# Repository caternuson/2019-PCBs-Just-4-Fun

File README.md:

# 2019-PCBs-Just-4-Fun
One PCB a month. Just 4 Fun.

# January

USB powered tamagotchi thing with an ATtiny85 brain.

# February

A backlit commemorative plaque thing.

# March
 <br/>
An IoT pyramid thing.

# April
 <br/>
Optical encoder reader with SPI interface.

# May
 <br/>
Terminal block to breadboard adapter.

# June
 <br/>
JST PH 4 to breadboard adapter.

# July
 <br/>
JST SH 4 to breadboard adapter.

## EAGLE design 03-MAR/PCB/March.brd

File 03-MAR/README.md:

# NOTES

The goal here was to utilize OSHPark's 3x board copy to make a pyramid.

My attempt at making break away mouse bites did not work. Ended up needing to dremel off the side triangles.

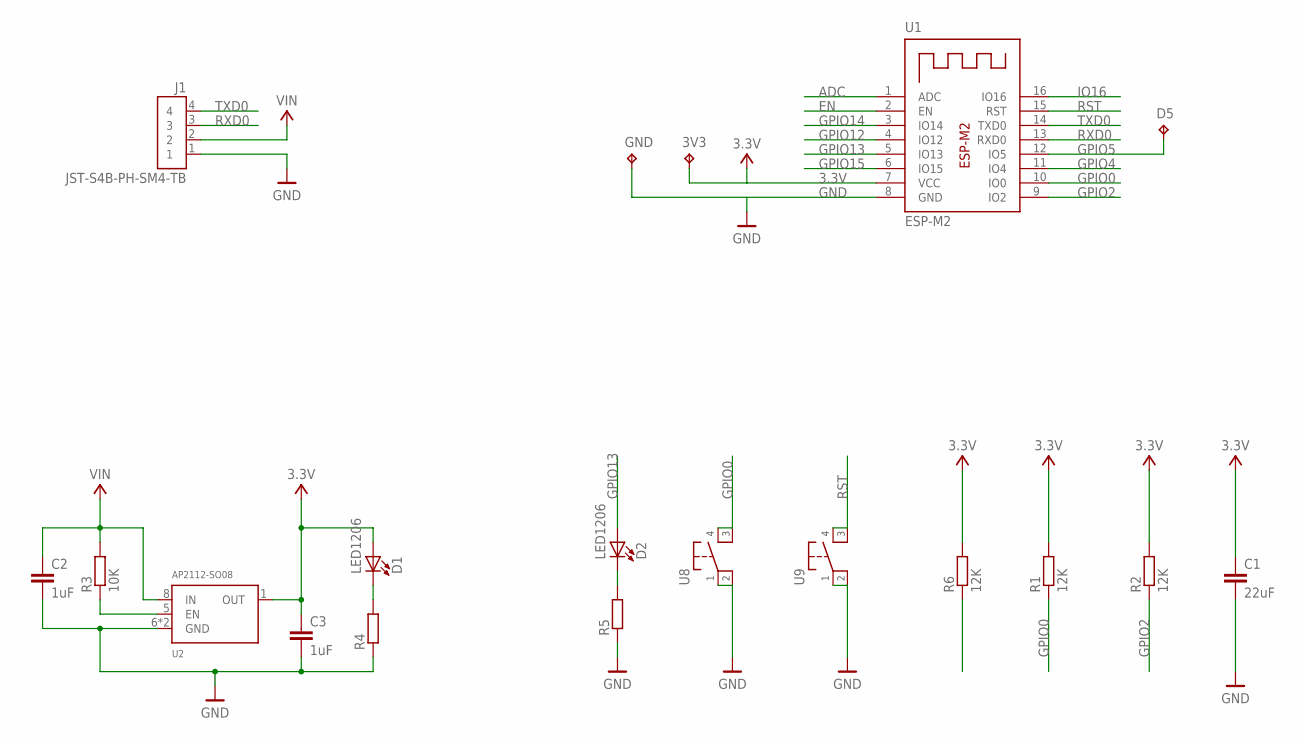
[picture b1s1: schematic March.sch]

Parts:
3V3: TPTP16R; TP16R
C1: 22uF; C1206
C2, C3: 1uF; C1206
D1, D2: LED1206
D5: TPTP16R; TP16R
GND: TPTP16R; TP16R
J1: JST-S4B-PH-SM4-TB
R1, R2, R6: 12K; R1206
R3: 10K; R1206
R4, R5: R-EU_R1206; R1206
U1: ESP-M2
U2: AP2112-SO08; SO08
U8, U9: PTS647

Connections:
3.3V: 3V3.TP, C1.1, C3.1, D1.2 (A), R1.2, R2.2, R6.2, U1.7 (VCC), U2.1 (OUT)
ADC: U1.1 (ADC)
EN: R6.1, U1.2 (EN)
GND: C1.2, C2.2, C3.2, GND.TP, J1.1, R4.1, R5.1, U1.8 (GND), U2.6 (GND), U2.7 (GND), U8.1, U8.2, U9.1, U9.2
GPIO0: R1.1, U1.10 (IO0), U8.3, U8.4
GPIO2: R2.1, U1.9 (IO2)
GPIO4: U1.11 (IO4)
GPIO5: D5.TP, U1.12 (IO5)
GPIO12: U1.4 (IO12)
GPIO13: D2.2 (A), U1.5 (IO13)
GPIO14: U1.3 (IO14)
GPIO15: U1.6 (IO15)
IO16: U1.16 (IO16)
unnamed: D1.1 (C), R4.2
unnamed: R3.1, U2.5 (EN)
unnamed: D2.1 (C), R5.2
RST: U1.15 (RST), U9.3, U9.4
RXD0: J1.3, U1.13 (RXD0)
TXD0: J1.4, U1.14 (TXD0)
VIN: C2.1, J1.2, R3.2, U2.8 (IN)

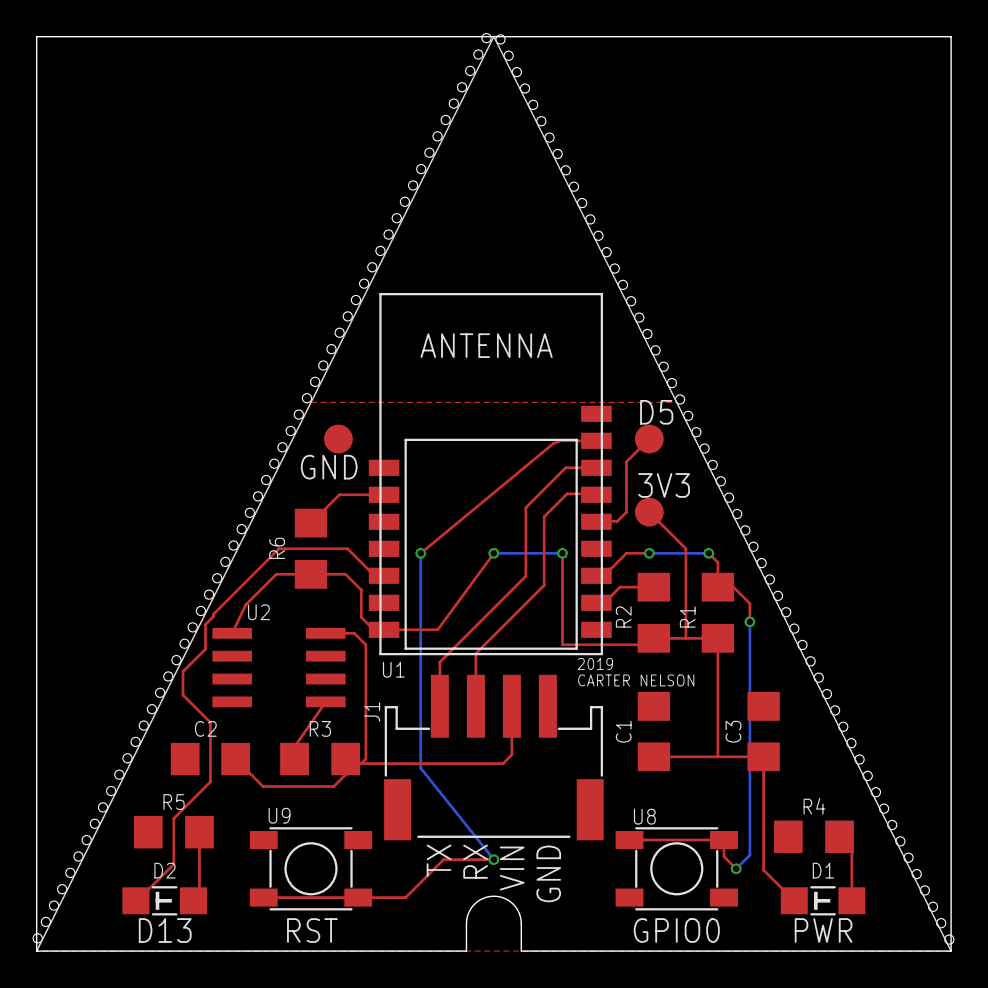
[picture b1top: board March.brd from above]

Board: 2 copper layers, 50.8 x 50.8 mm, 19 parts (0 on the bottom side), 14 nets.

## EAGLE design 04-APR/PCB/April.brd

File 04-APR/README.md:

# NOTES

The goal here was to make a functional breakout for the LS7366R.

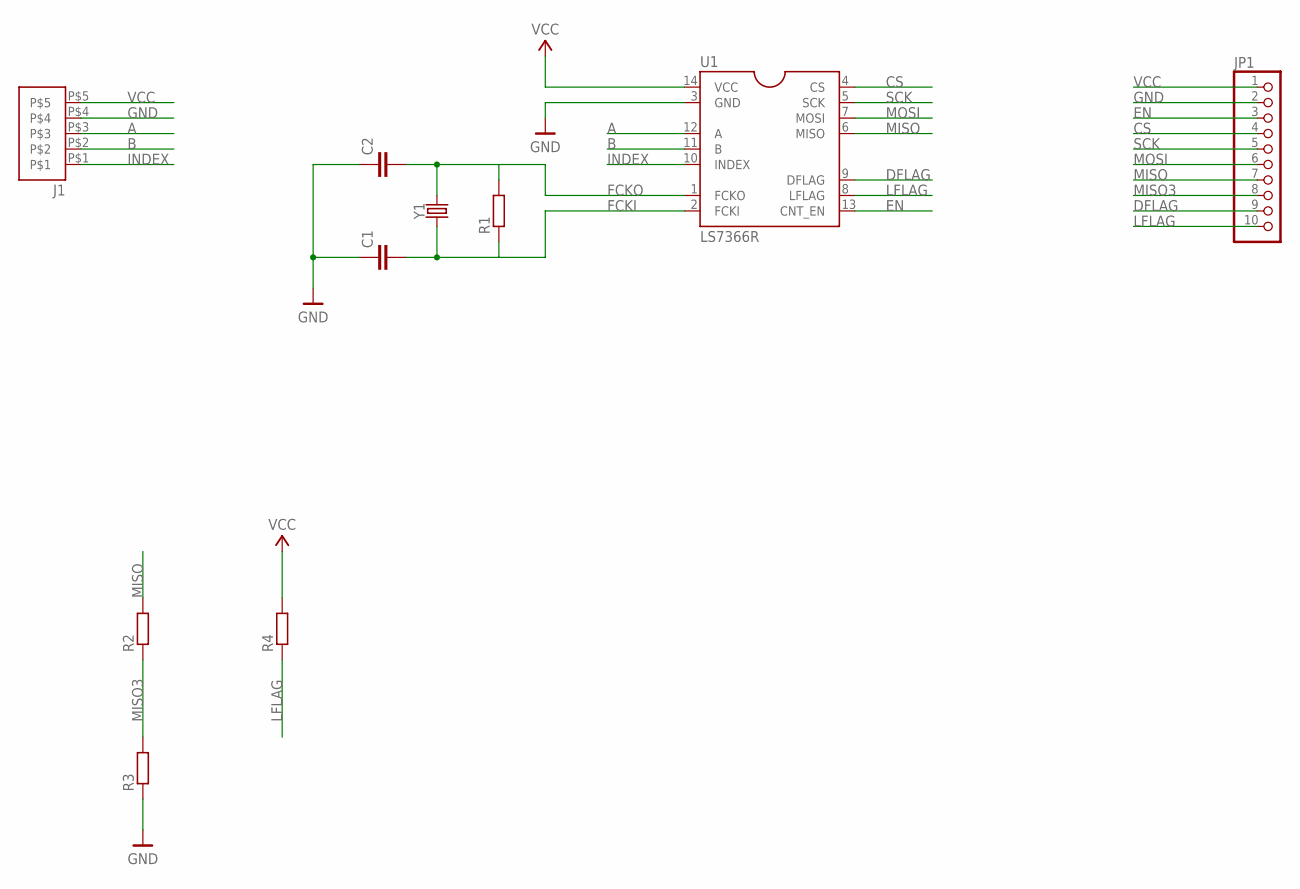
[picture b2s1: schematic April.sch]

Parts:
C1, C2: C-EU050-024X044; C050-024X044
J1: AF-PID2319; TB-01-5
JP1: PINHD-1X10; 1X10
R1, R2, R3, R4: R-EU_0207/10; 0207/10
U1: LS7366R; DIL14
Y1: CRYSTALPTH-HC49US; HC49US

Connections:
A: J1.P$3, U1.12 (A)
B: J1.P$2, U1.11 (B)
CS: JP1.4, U1.4 (CS)
DFLAG: JP1.9, U1.9 (DFLAG)
EN: JP1.3, U1.13 (CNT_EN)
FCKI: C1.2, R1.1, U1.2 (FCKI), Y1.1
FCKO: C2.2, R1.2, U1.1 (FCKO), Y1.2
GND: C1.1, C2.1, J1.P$4, JP1.2, R3.1, U1.3 (GND)
INDEX: J1.P$1, U1.10 (INDEX)
LFLAG: JP1.10, R4.1, U1.8 (LFLAG)
MISO: JP1.7, R2.2, U1.6 (MISO)
MISO3: JP1.8, R2.1, R3.2
MOSI: JP1.6, U1.7 (MOSI)
SCK: JP1.5, U1.5 (SCK)
VCC: J1.P$5, JP1.1, R4.2, U1.14 (VCC)

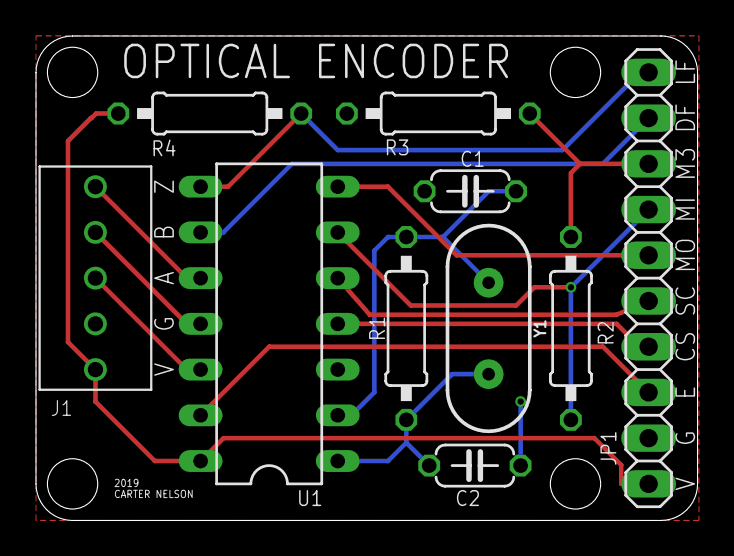
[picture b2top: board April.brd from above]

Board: 2 copper layers, 36.8 x 26.9 mm, 10 parts (0 on the bottom side), 15 nets.

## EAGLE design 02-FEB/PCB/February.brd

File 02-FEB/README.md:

# NOTES

The goal here was to work on the process for bringing in custom art for silk, etc.

### The Process
This process could be generalized to anything that produces a BMP. However, using Inkscape made setting the document properties easier.

* Inkscape
  * Set up document to match board dimensions
  * Make drawing
  * Export PNG
  * Set DPI, ex: 300
* Convert to BMP
  * since Inkscape only exports PNG and Eagle only imports BMP
  * linux convert
    * `convert bitmap.png -background white -alpha remove -alpha off -colors 2 bitmap.bmp`
  * Gimp (old)
    * Convert PNG to BMP
    * Reduce colors
      * Image -> Mode -> Indexed
      * set Maximum number of colors to something small
* Eagle
  * File -> Import -> Bitmap...
  * match DPI to above
  * pick color and destination layer

### Multi-layer specifics
When you import the BMP into Eagle you can specify any destination layer. This lets you
get creative with things like the stop layer to expose copper. The general process that
was done for this board went something like:

* Inkscape
  * Create layers to match the Eagle layers names
    * tPlace
    * tStop
    * etc.
  * Set the colors for these layers to match board fab
    * tPlace = white for silk
    * tStop = yellow-ish for exposed copper
  * Make the layer specific drawings on these layers
  * Output multipe PNGs
    * Turn off all other layers
    * Export to PNG with visible layer name, ex: tPlace.png
  * Convert PNGs as above
  * When importing in Eagle, match the name to the layer

For example, these were the BMPs used for the top silk layer:

and the top stop layer:

which combined to form the white silk and exposed copper:

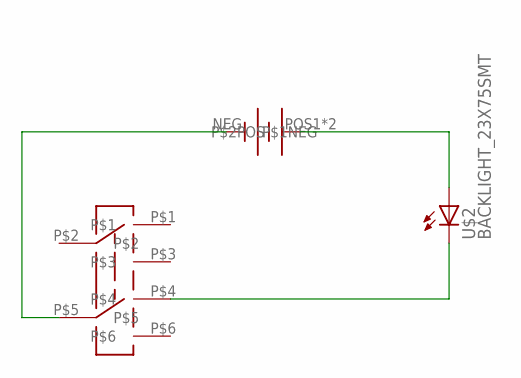
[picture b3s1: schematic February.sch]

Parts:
U$1: JS202011SCQN
U$2: BACKLIGHT_23X75SMT
U$3: BK-912

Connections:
GND: U$1.P$5, U$3.NEG (P$1NEG)
unnamed: U$2.LED+ (A), U$3.POS1 (P$2POS), U$3.POS2 (P$2POS)
VBAT: U$1.P$4, U$2.LED- (C)

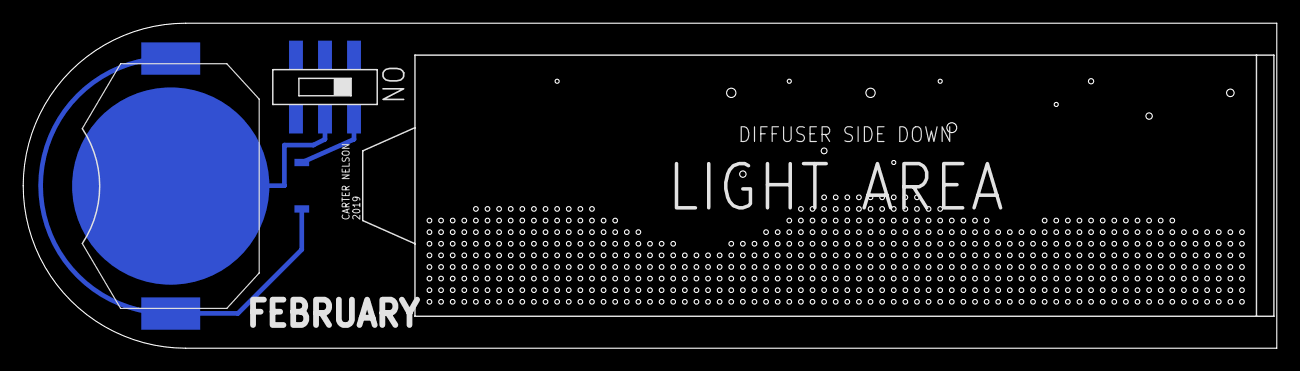
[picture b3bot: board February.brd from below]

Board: 2 copper layers, 108.0 x 28.0 mm, 3 parts (3 on the bottom side), 3 nets.

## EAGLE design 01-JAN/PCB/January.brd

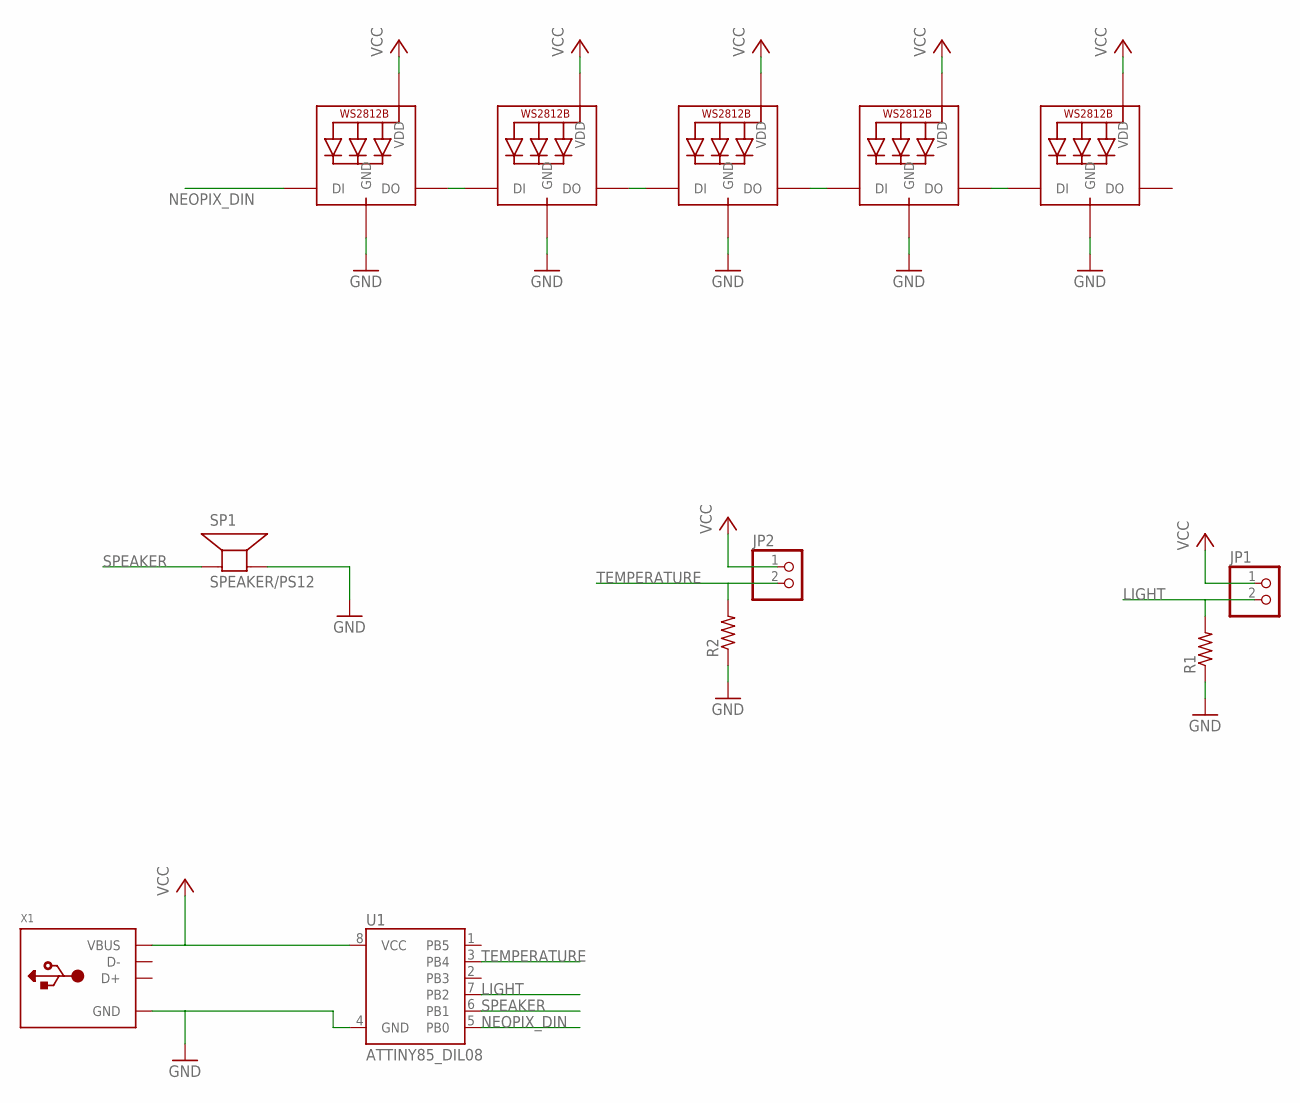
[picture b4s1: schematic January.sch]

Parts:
JP1, JP2: PINHD-1X2; 1X02
NEO0, NEO1, NEO2, NEO3, NEO4: NEOPIXEL_5MM; LED5MM_4PIN
R1, R2: R-US_0207/10; 0207/10
SP1: SPEAKER/PS12; PS12
U1: ATTINY85_DIL08; DIL08
X1: MICROBUILDER_USB_TYPEAPCB; MICROBUILDER_USBA_PCB

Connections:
GND: NEO0.G (GND), NEO1.G (GND), NEO2.G (GND), NEO3.G (GND), NEO4.G (GND), R1.1, R2.1, SP1.P$2 (-), U1.4 (GND), X1.GND
LIGHT: JP1.2, R1.2, U1.7 (PB2)
unnamed: NEO0.DO, NEO1.DI
unnamed: NEO1.DO, NEO2.DI
unnamed: NEO2.DO, NEO3.DI
unnamed: NEO3.DO, NEO4.DI
NEOPIX_DIN: NEO0.DI, U1.5 (PB0)
SPEAKER: SP1.P$1 (+), U1.6 (PB1)
TEMPERATURE: JP2.2, R2.2, U1.3 (PB4)
VCC: JP1.1, JP2.1, NEO0.5V (VDD), NEO1.5V (VDD), NEO2.5V (VDD), NEO3.5V (VDD), NEO4.5V (VDD), U1.8 (VCC), X1.VCC (VBUS)

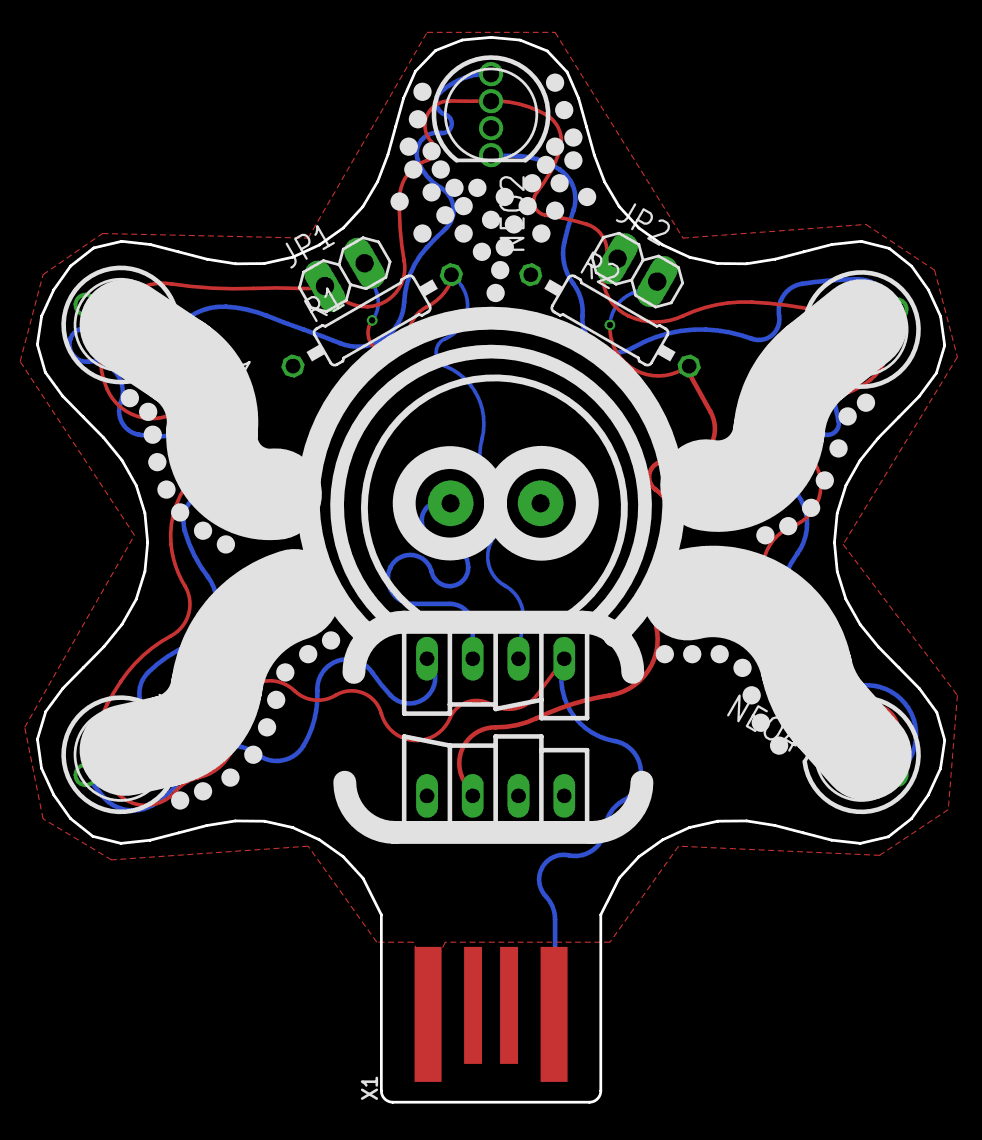
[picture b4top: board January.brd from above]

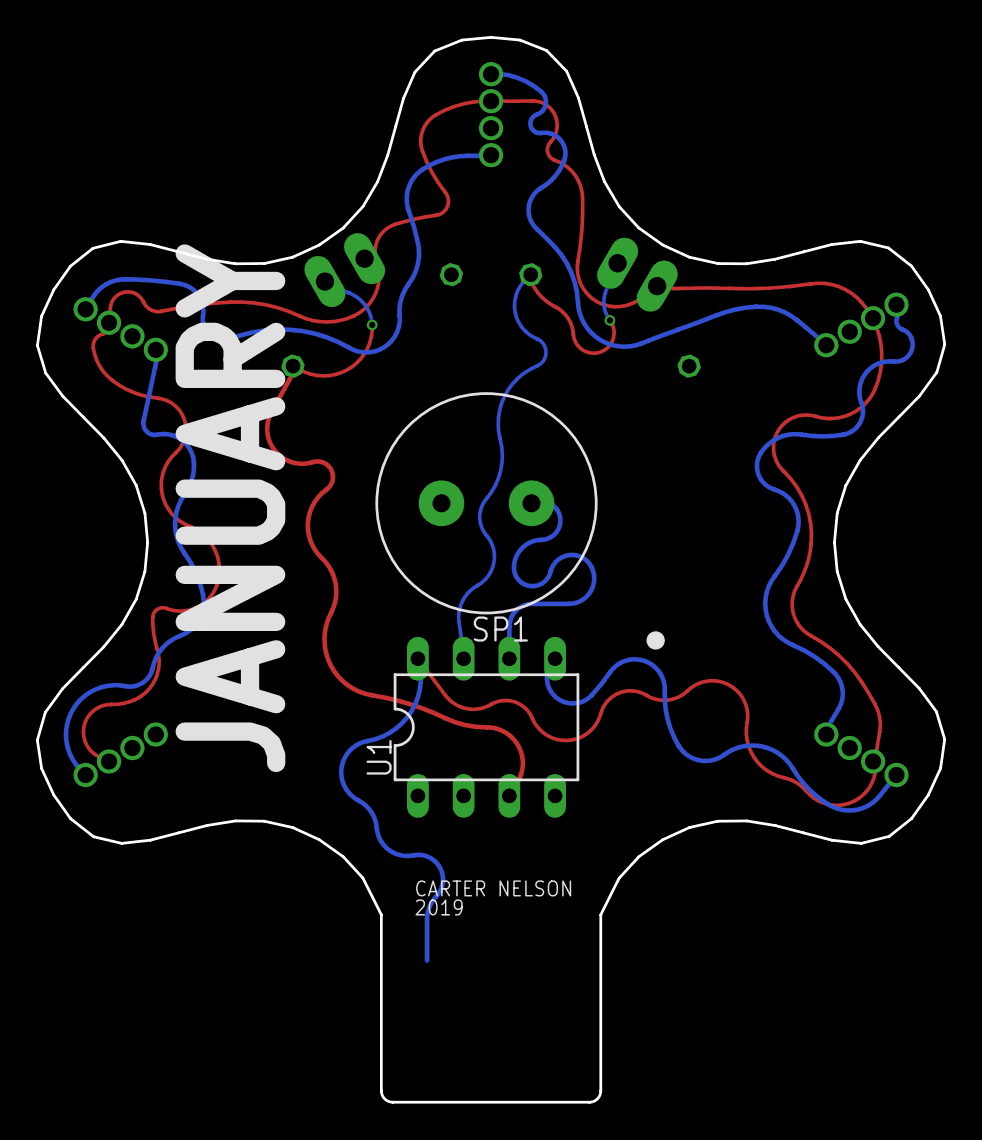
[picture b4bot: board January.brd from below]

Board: 2 copper layers, 50.4 x 59.2 mm, 12 parts (2 on the bottom side), 10 nets.

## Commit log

2019-02-09 Add January
2019-02-16 add how to info for JAN
2019-02-16 move readme
2019-04-20 add February
2019-04-20 change thumbnails to fixed height
2019-04-20 updated FEB doc
2019-04-20 fix path
2019-04-20 tweak md images
2019-05-02 few more sent to fab
2019-08-09 even more
2019-08-09 doc update
2019-08-13 another one

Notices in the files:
parts and their libraries:
SparkFun-Clocks: Licensing: Creative Commons ShareAlike 4.0 International - https://creativecommons.org/licenses/by-sa/4.0
